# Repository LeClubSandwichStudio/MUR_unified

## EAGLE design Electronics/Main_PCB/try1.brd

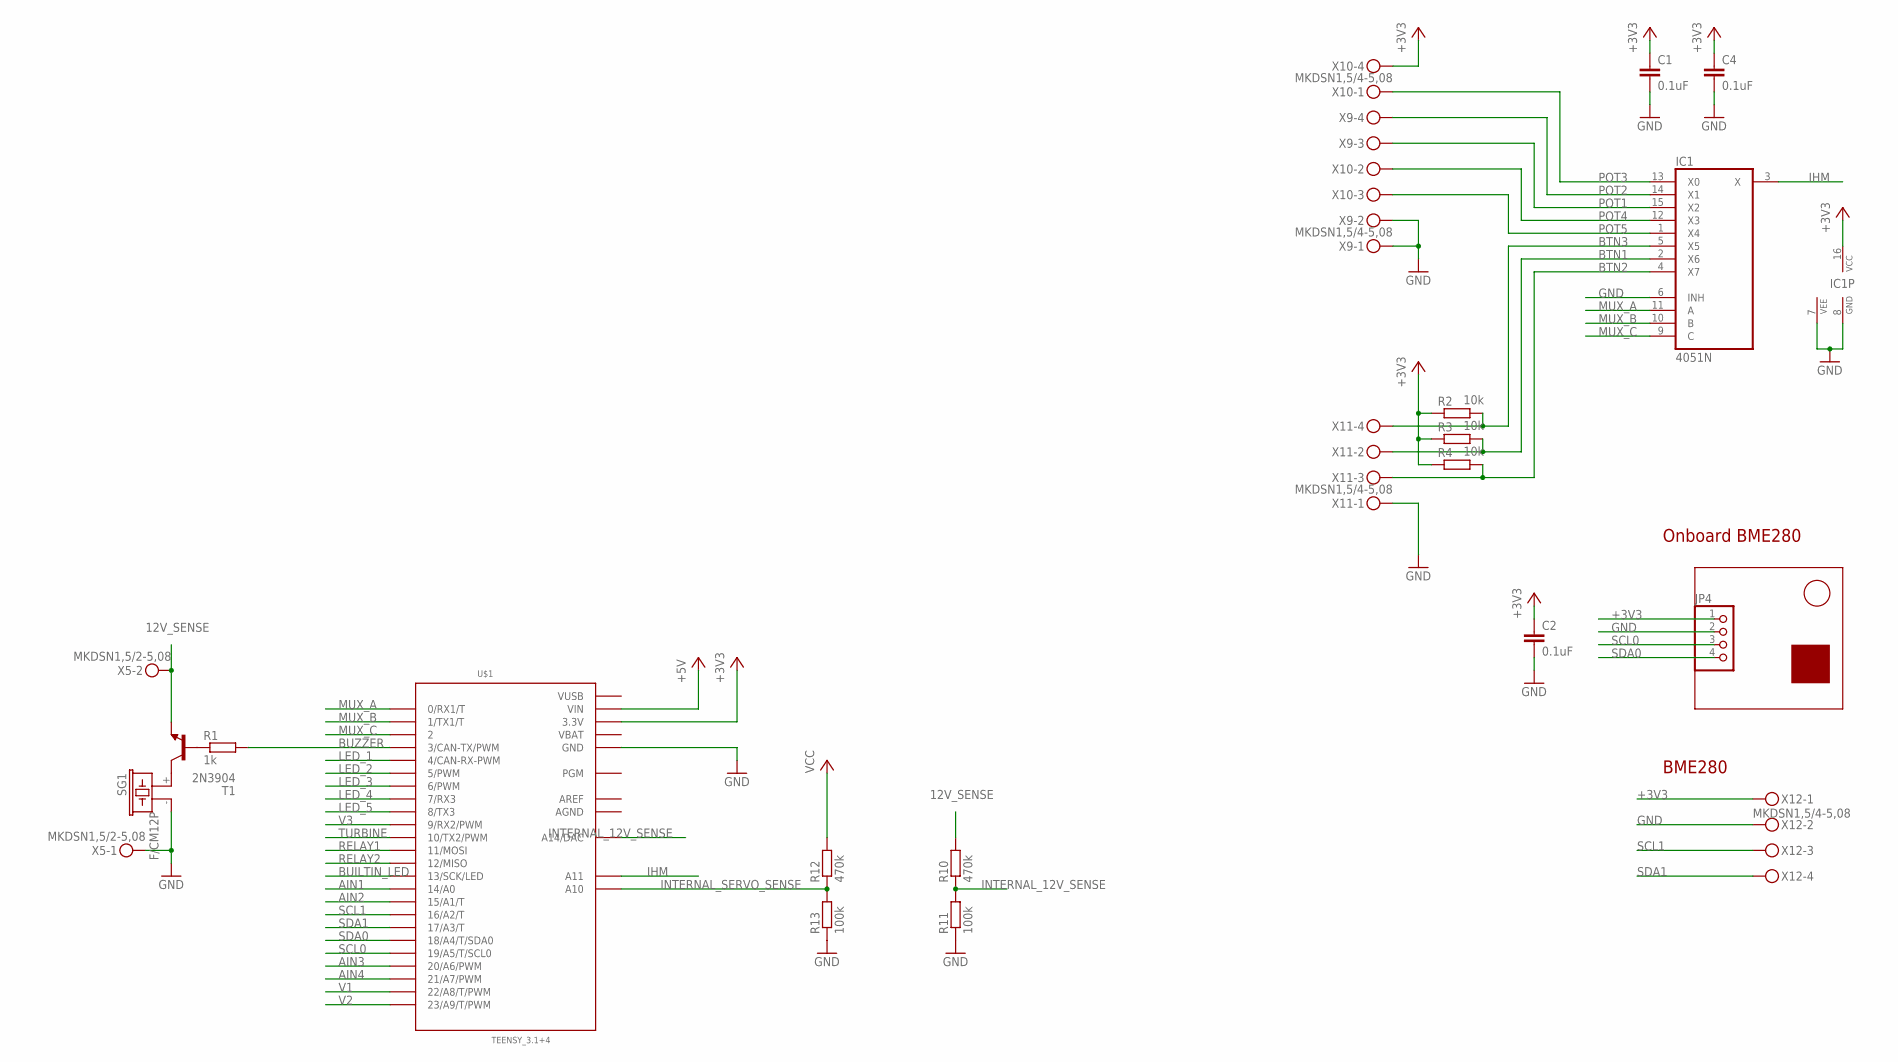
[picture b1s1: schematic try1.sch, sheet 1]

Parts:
C1, C2, C4: 0.1uF; C050-024X044
IC1: 4051N; DIL16
JP4: PINHD-1X4; 1X04
R1: 1k; 0207/15
R2, R3, R4: 10k; 0204/7
R10, R12: 470k; 0207/12
R11, R13: 100k; 0207/12
SG1: F/CM12P
T1: 2N3904; TO92
U$1: TEENSY_3.1+4
X5: MKDSN1,5/2-5,08
X9, X10, X11, X12: MKDSN1,5/4-5,08

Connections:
12V_SENSE: R10.2, T1.3 (E), X5.2
+3V3: C1.1, C2.1, C4.1, IC1.16 (VCC), JP4.1, R2.1, R3.1, R4.1, U$1.3.3V, U$1.3.3V1 (3.3V), X10.4, X12.1; also elsewhere on the board
+5V: U$1.VIN; also elsewhere on the board
AGND: U$1.AGND
AIN1: U$1.14/A0; also elsewhere on the board
AIN2: U$1.15/A1 (15/A1/T); also elsewhere on the board
AIN3: U$1.20/A6 (20/A6/PWM); also elsewhere on the board
AIN4: U$1.21/A7 (21/A7/PWM); also elsewhere on the board
AREF: U$1.AREF
BTN1: IC1.2 (X6), R3.2, X11.2
BTN2: IC1.4 (X7), R4.2, X11.3
BTN3: IC1.5 (X5), R2.2, X11.4
BUILTIN_LED: U$1.13 (13/SCK/LED)
BUZZER: R1.2, U$1.3 (3/CAN-TX/PWM)
GND: C1.2, C2.2, C4.2, IC1.6 (INH), IC1.7 (VEE), IC1.8 (GND), JP4.2, R11.1, R13.1, SG1.- (2), U$1.GND, U$1.GND1 (GND), X5.1, X9.1, X9.2, X11.1, X12.2; also elsewhere on the board
IHM: IC1.3 (X), U$1.A11
INTERNAL_12V_SENSE: R10.1, R11.2, U$1.A14 (A14/DAC)
INTERNAL_SERVO_SENSE: R12.1, R13.2, U$1.A10
LED_1: U$1.4 (4/CAN-RX-PWM); also elsewhere on the board
LED_2: U$1.5 (5/PWM); also elsewhere on the board
LED_3: U$1.6 (6/PWM); also elsewhere on the board
LED_4: U$1.7 (7/RX3); also elsewhere on the board
LED_5: U$1.8 (8/TX3); also elsewhere on the board
MUX_A: IC1.11 (A), U$1.0 (0/RX1/T)
MUX_B: IC1.10 (B), U$1.1 (1/TX1/T)
MUX_C: IC1.9 (C), U$1.2
unnamed: R1.1, T1.2 (B)
unnamed: SG1.+ (1), T1.1 (C)
POT1: IC1.15 (X2), X9.3
POT2: IC1.14 (X1), X9.4
POT3: IC1.13 (X0), X10.1
POT4: IC1.12 (X3), X10.2
POT5: IC1.1 (X4), X10.3
RELAY1: U$1.11 (11/MOSI); also elsewhere on the board
RELAY2: U$1.12 (12/MISO); also elsewhere on the board
SCL0: JP4.3, U$1.19/A5 (19/A5/T/SCL0)
SCL1: U$1.16/A2 (16/A2/T), X12.3
SDA0: JP4.4, U$1.18/A4 (18/A4/T/SDA0)
SDA1: U$1.17/A3 (17/A3/T), X12.4
TURBINE: U$1.10 (10/TX2/PWM); also elsewhere on the board
V1: U$1.22/A8 (22/A8/T/PWM); also elsewhere on the board
V2: U$1.23/A9 (23/A9/T/PWM); also elsewhere on the board
V3: U$1.9 (9/RX2/PWM); also elsewhere on the board
VBAT: U$1.VBAT
VCC: R12.2; also elsewhere on the board
VUSB: U$1.VUSB

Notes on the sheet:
Onboard BME280
BME280

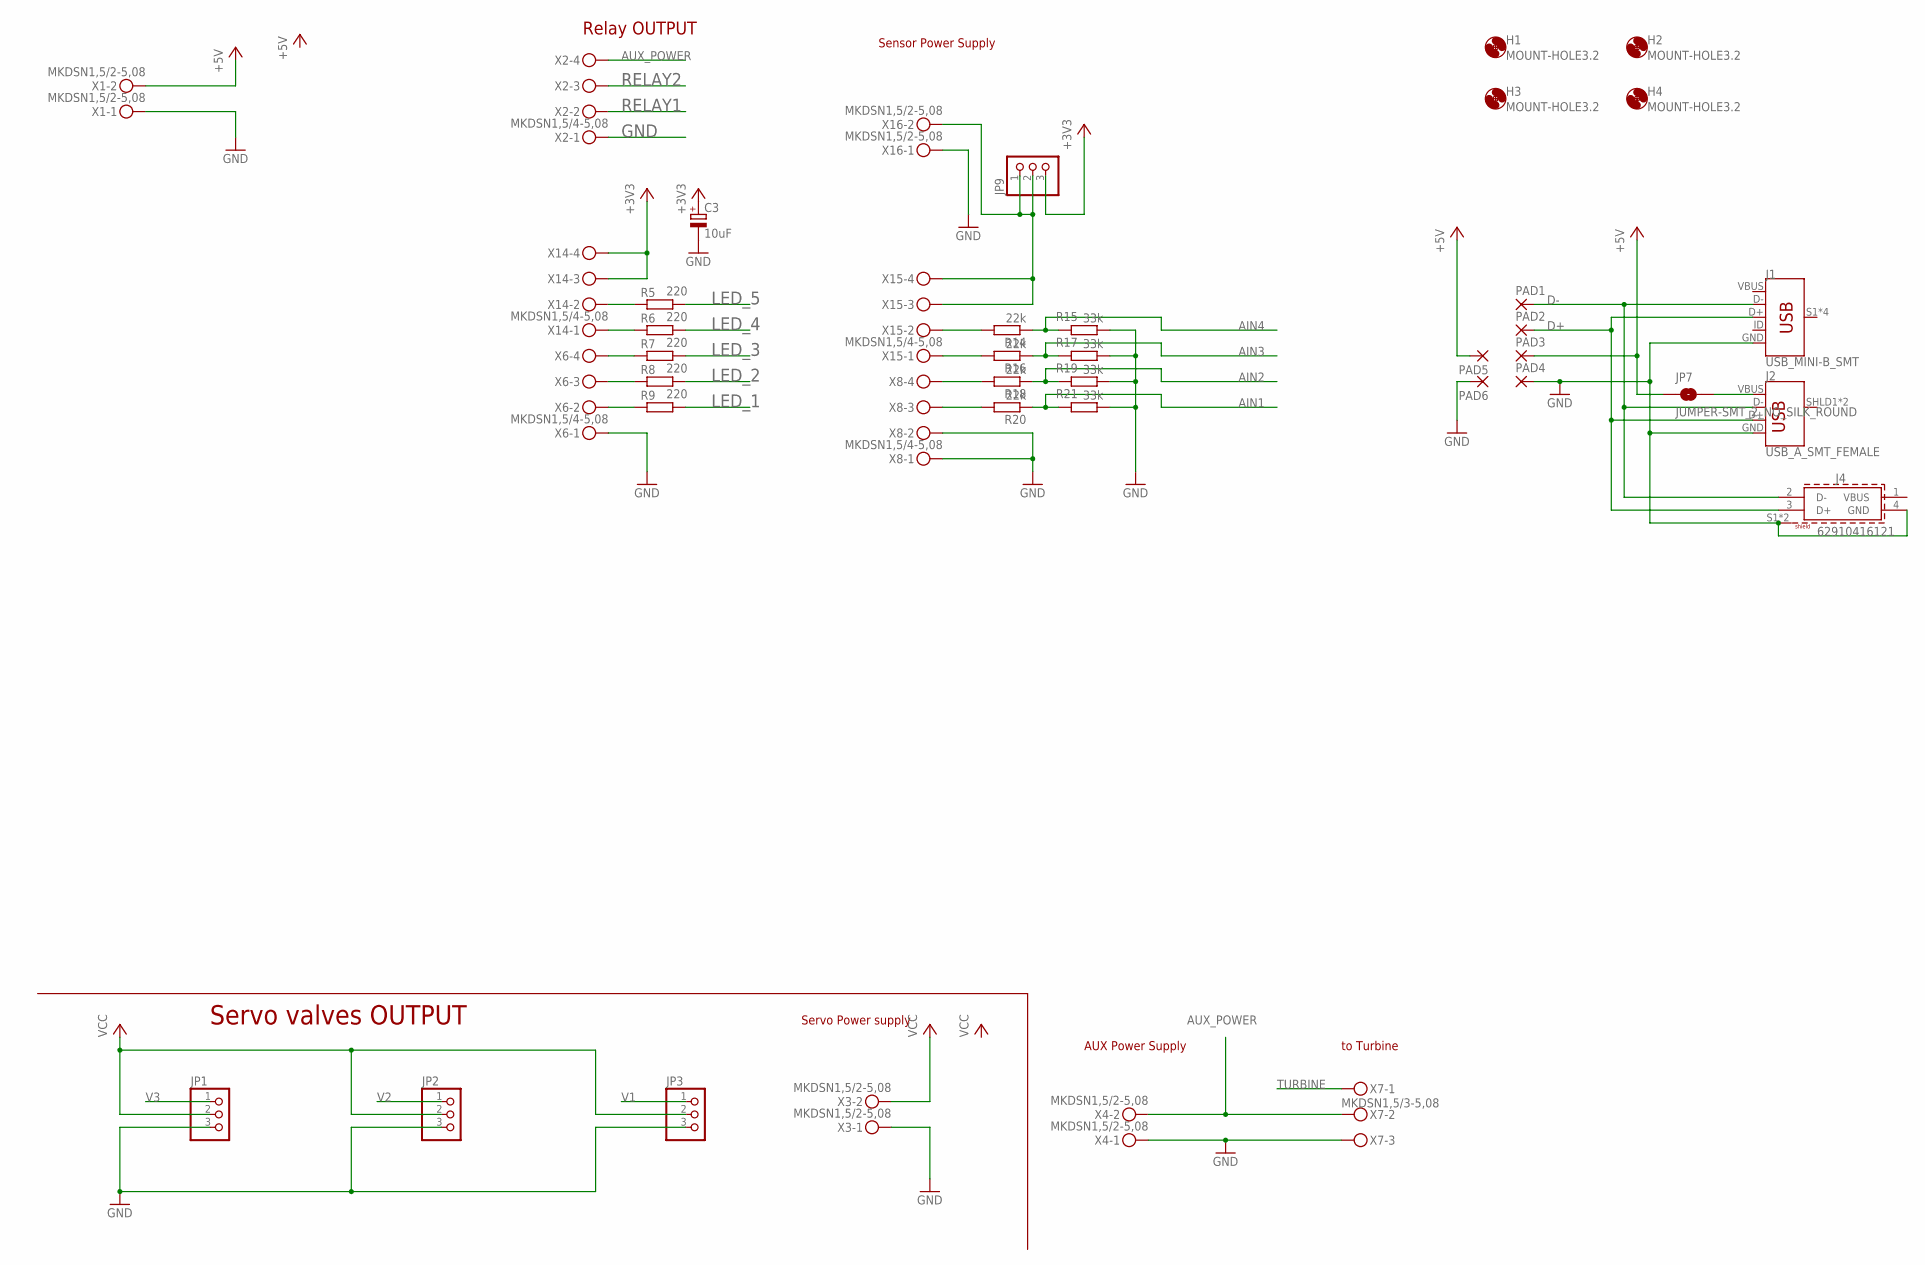
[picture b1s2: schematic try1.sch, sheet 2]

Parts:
C3: 10uF; E2,5-7
H1, H2, H3, H4: MOUNT-HOLE3.2; 3,2
J1: USB_MINI-B_SMT; USB-MINIB
J2: USB_A_SMT_FEMALE; USB-A-S-SILK-FEMALE
J4: 62910416121
JP1, JP2, JP3: PINHD-1X3/90; 1X03/90
JP7: JUMPER-SMT_2_NO_SILK_ROUND; SMT-JUMPER_2_NO_SILK_ROUND
JP9: PINHD-1X3; 1X03
PAD1, PAD2, PAD3, PAD4, PAD5, PAD6: 3,17/1,3
R5, R6, R7, R8, R9: 220; 0207/15
R14, R16, R18, R20: 22k; 0207/12
R15, R17, R19, R21: 33k; 0207/12
X1, X3, X4, X16: MKDSN1,5/2-5,08
X2, X6, X8, X14, X15: MKDSN1,5/4-5,08
X7: MKDSN1,5/3-5,08

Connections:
+3V3: C3.+, JP9.3, X14.3, X14.4; also elsewhere on the board
+5V: JP7.1, PAD3.1, PAD5.1, X1.2; also elsewhere on the board
AIN1: R20.1, R21.2; also elsewhere on the board
AIN2: R18.1, R19.2; also elsewhere on the board
AIN3: R16.1, R17.2; also elsewhere on the board
AIN4: R14.1, R15.2; also elsewhere on the board
AUX_POWER: X2.4, X4.2, X7.2
D+: J1.D+, J2.D+, J4.3 (D+), PAD2.1
D-: J1.D-, J2.D-, J4.2 (D-), PAD1.1
GND: C3.-, J1.GND, J2.GND, J4.4 (GND), J4.S1 (SHIELD), J4.S2 (SHIELD), JP1.3, JP2.3, JP3.3, PAD4.1, PAD6.1, R15.1, R17.1, R19.1, R21.1, X1.1, X2.1, X3.1, X4.1, X6.1, X7.3, X8.1, X8.2, X16.1; also elsewhere on the board
LED_1: R9.2; also elsewhere on the board
LED_2: R8.2; also elsewhere on the board
LED_3: R7.2; also elsewhere on the board
LED_4: R6.2; also elsewhere on the board
LED_5: R5.2; also elsewhere on the board
unnamed: R5.1, X14.2
unnamed: R6.1, X14.1
unnamed: R7.1, X6.4
unnamed: R8.1, X6.3
unnamed: R9.1, X6.2
unnamed: JP9.1, JP9.2, X15.3, X15.4, X16.2
unnamed: R20.2, X8.3
unnamed: R18.2, X8.4
unnamed: R16.2, X15.1
unnamed: R14.2, X15.2
unnamed: J2.VBUS, JP7.2
RELAY1: X2.2; also elsewhere on the board
RELAY2: X2.3; also elsewhere on the board
TURBINE: X7.1; also elsewhere on the board
V1: JP3.1; also elsewhere on the board
V2: JP2.1; also elsewhere on the board
V3: JP1.1; also elsewhere on the board
VBUS: J1.VBUS
VCC: JP1.2, JP2.2, JP3.2, X3.2; also elsewhere on the board

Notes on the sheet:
Servo valves OUTPUT
Relay OUTPUT
Servo Power supply
AUX Power Supply
to Turbine
Sensor Power Supply

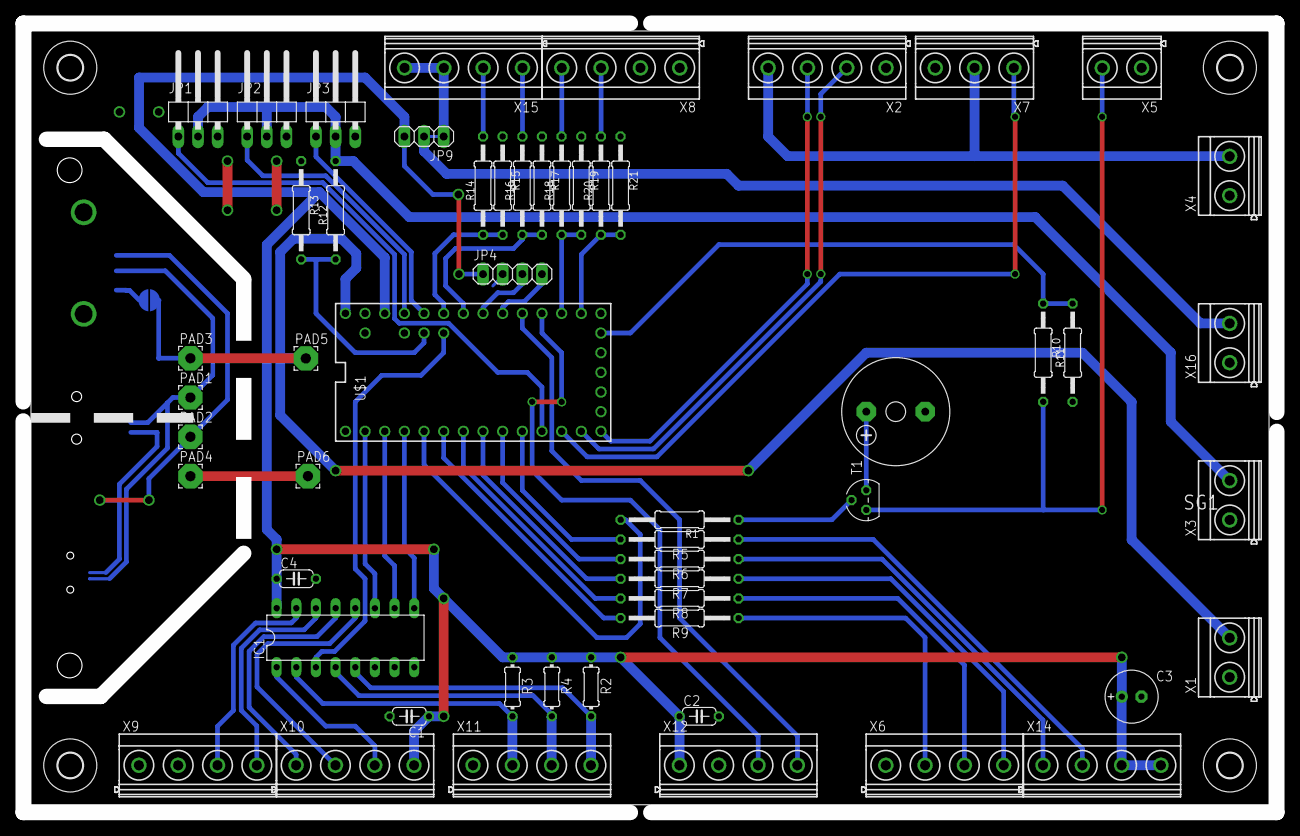
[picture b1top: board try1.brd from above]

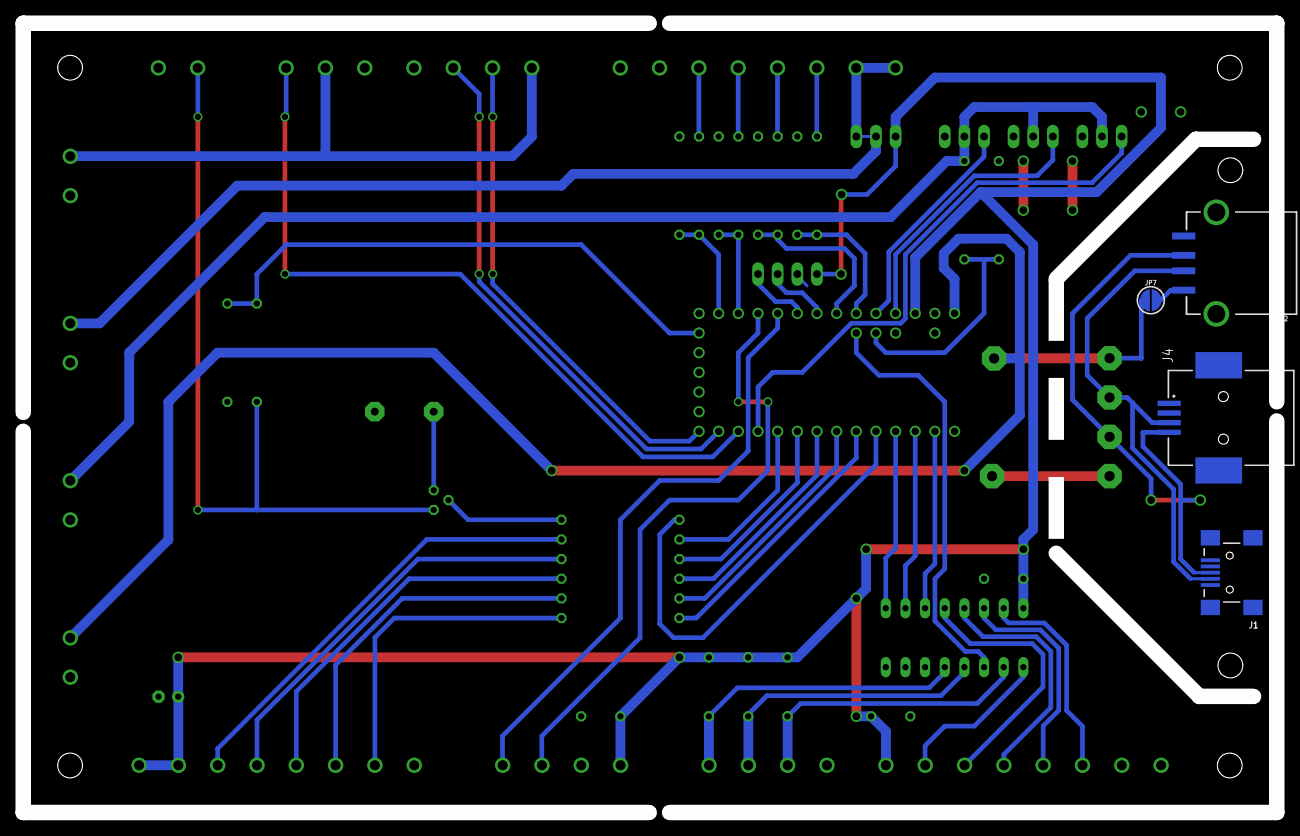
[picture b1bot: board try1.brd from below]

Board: 2 copper layers, 162.0 x 102.0 mm, 63 parts (4 on the bottom side), 55 nets.

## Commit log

2020-11-27 added commented code from @smile5 OMYXAir github
2020-12-11 WIP main PCB
2020-12-15 try1 finished, HW tests required

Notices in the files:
parts and their libraries:
SparkFun-Jumpers: Licensing: Creative Commons ShareAlike 4.0 International - https://creativecommons.org/licenses/by-sa/4.0
Wurth_Connectors_WR-USB: Copyright: Würth Elektronik
